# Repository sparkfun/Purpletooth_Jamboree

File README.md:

Purpletooth Jamboree Development Board
==================

Audio support board for the BC127 module from BlueCreation.

[  
*Purpletooth Jamboree Development Board*](https://www.sparkfun.com/products/11924)

Design files and firmware files for the [Purpletooth Jamboree Development Board](https://www.sparkfun.com/products/11924).

Repository Contents
-------------------

* **/Fritzing** - Fritzing components for this board
* **/Hardware** - Eagle PCB layout files
* **/Libraries** - Library files for various platforms
* **/Production** - Files to support SparkFun production

License Information
-------------------

All contents of this repository are released under [Creative Commons Share-alike 4.0](http://creativecommons.org/licenses/by-sa/4.0/).

Authors: Mike Hord @ SparkFun Electonics

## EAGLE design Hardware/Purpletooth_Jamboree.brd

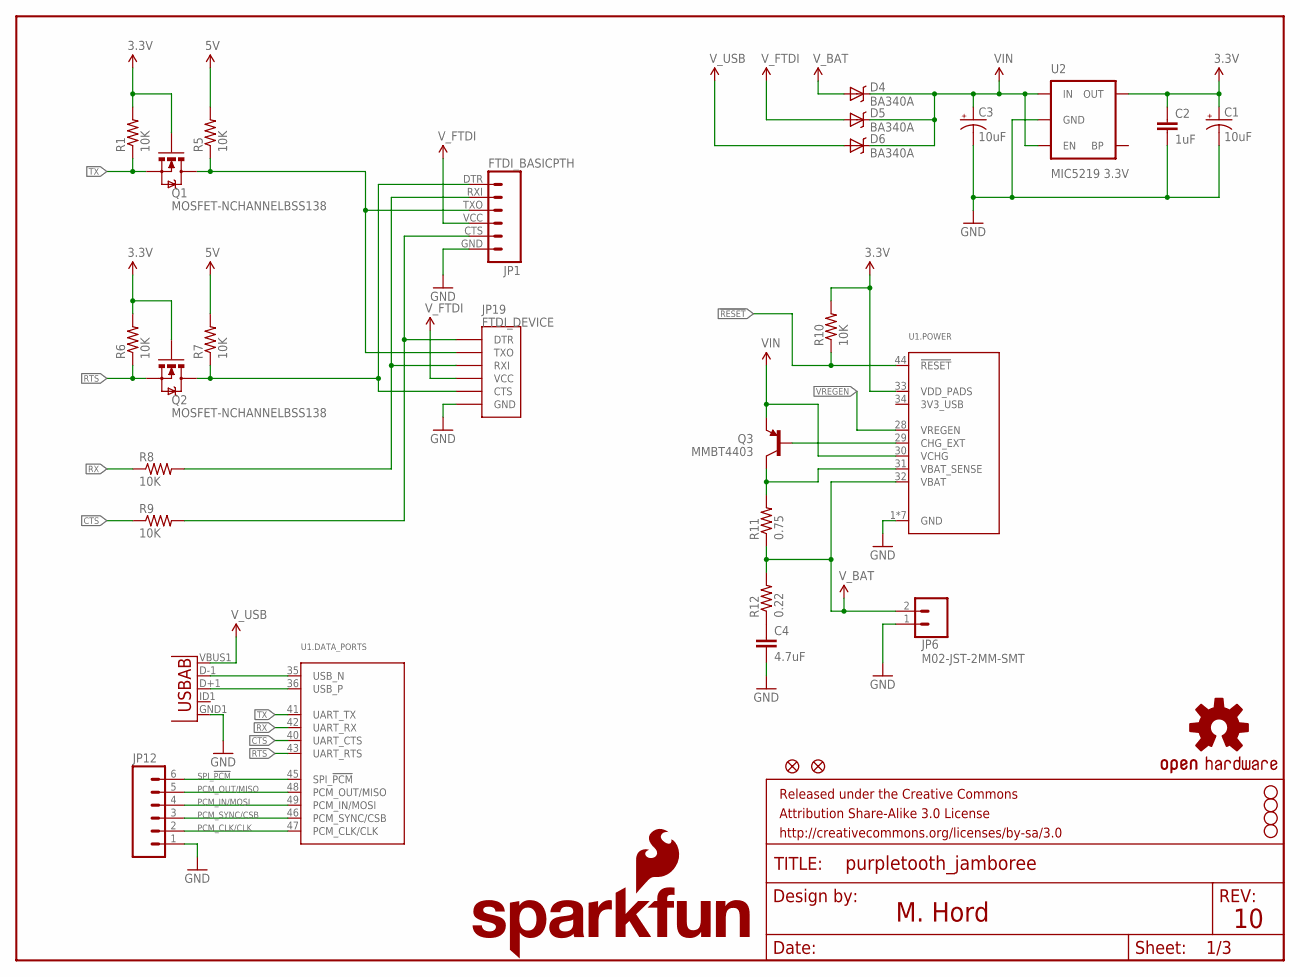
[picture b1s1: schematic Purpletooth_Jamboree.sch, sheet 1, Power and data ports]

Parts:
C1, C3: 10uF; EIA3216
C2: 1uF; 0805
C4: 4.7uF; 0603-CAP
D4, D5, D6: BA340A; SMA-DIODE
FID1, FID2: FIDUCIALUFIDUCIAL; MICRO-FIDUCIAL
FRAME1: FRAME-LETTER; CREATIVE_COMMONS
JP1: FTDI_BASICPTH; FTDI_BASIC
JP2: USB-ABCONN-11794; USB-AB-MICRO-SMD_V03
JP6: M02-JST-2MM-SMT; JST-2-SMD
JP12: M06SIP; 1X06
JP19: FTDI_DEVICE; FTDI_DEVICE_SIDE
LOGO1: OSHW-LOGOM; OSHW-LOGO-M
LOGO2: SFE_LOGO_NAME_FLAME.2_INCH; SFE_LOGO_NAME_FLAME_.2
Q1, Q2: MOSFET-NCHANNELBSS138; SOT23
Q3: MMBT4403; SOT23
R1, R5, R6, R7, R8, R9, R10: 10K; 0603-RES
R11: 0.75; 0805
R12: 0.22; 0805
STANDOFF1, STANDOFF2, STANDOFF3, STANDOFF4: STAND-OFF
U1: BC127EXTRA_PASTE; BC127_XTRA_PASTE
U2: MIC5219 3.3V; SOT23-5

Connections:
3.3V: C1.A (+), C2.1, Q1.1 (G), Q2.1 (G), R1.2, R6.2, R10.2, U1.33 (VDD_PADS), U2.5 (OUT); also elsewhere on the board
5V_CTS: JP1.CTS (5), JP19.P$1 (DTR), R9.2
5V_RTS: JP1.DTR (1), JP19.P$5 (CTS), Q2.3 (D), R7.1
5V_RX: JP1.RXI (2), JP19.P$3 (RXI), R8.2
5V_TX: JP1.TXO (3), JP19.P$2 (TXO), Q1.3 (D), R5.1
!RESET: R10.1, U1.44 (!RESET); also elsewhere on the board
CHG_EXT: Q3.1 (B), U1.29 (CHG_EXT)
CTS: R9.1, U1.40 (UART_CTS)
GND: C1.C (-), C2.2, C3.C (-), C4.2, JP1.GND (6), JP2.GND1 (GND), JP6.1 (2), JP12.1, JP19.P$6 (GND), U1.1 (GND), U1.2 (GND), U1.3 (GND), U1.4 (GND), U1.11 (GND), U1.22 (GND), U1.27 (GND), U2.2 (GND); also elsewhere on the board
unnamed: C4.1, R12.1
PCM_CLK/CLK: JP12.2, U1.47 (PCM_CLK/CLK)
PCM_IN/MOSI: JP12.4, U1.49 (PCM_IN/MOSI)
PCM_OUT/MISO: JP12.5, U1.48 (PCM_OUT/MISO)
PCM_SYNC/CSB: JP12.3, U1.46 (PCM_SYNC/CSB)
RTS: Q2.2 (S), R6.1, U1.43 (UART_RTS)
RX: R8.1, U1.42 (UART_RX)
SPI_!PCM: JP12.6, U1.45 (SPI_!PCM)
TX: Q1.2 (S), R1.1, U1.41 (UART_TX)
USB_N: JP2.D-1 (D-), U1.35 (USB_N)
USB_P: JP2.D+1 (D+), U1.36 (USB_P)
VBAT_SENSE: Q3.3 (C), R11.2, U1.31 (VBAT_SENSE)
VIN: C3.A (+), D4.C, D5.C, D6.C, Q3.2 (E), R5.2, R7.2, U1.30 (VCHG), U2.1 (IN), U2.3 (EN); also elsewhere on the board
VREGEN: U1.28 (VREGEN); also elsewhere on the board
V_BAT: D4.A, JP6.2 (1), R11.1, R12.2, U1.32 (VBAT)
V_FTDI: D5.A, JP1.VCC (4), JP19.P$4 (VCC)
V_USB: D6.A, JP2.VBUS1 (VBUS)

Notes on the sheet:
M. Hord

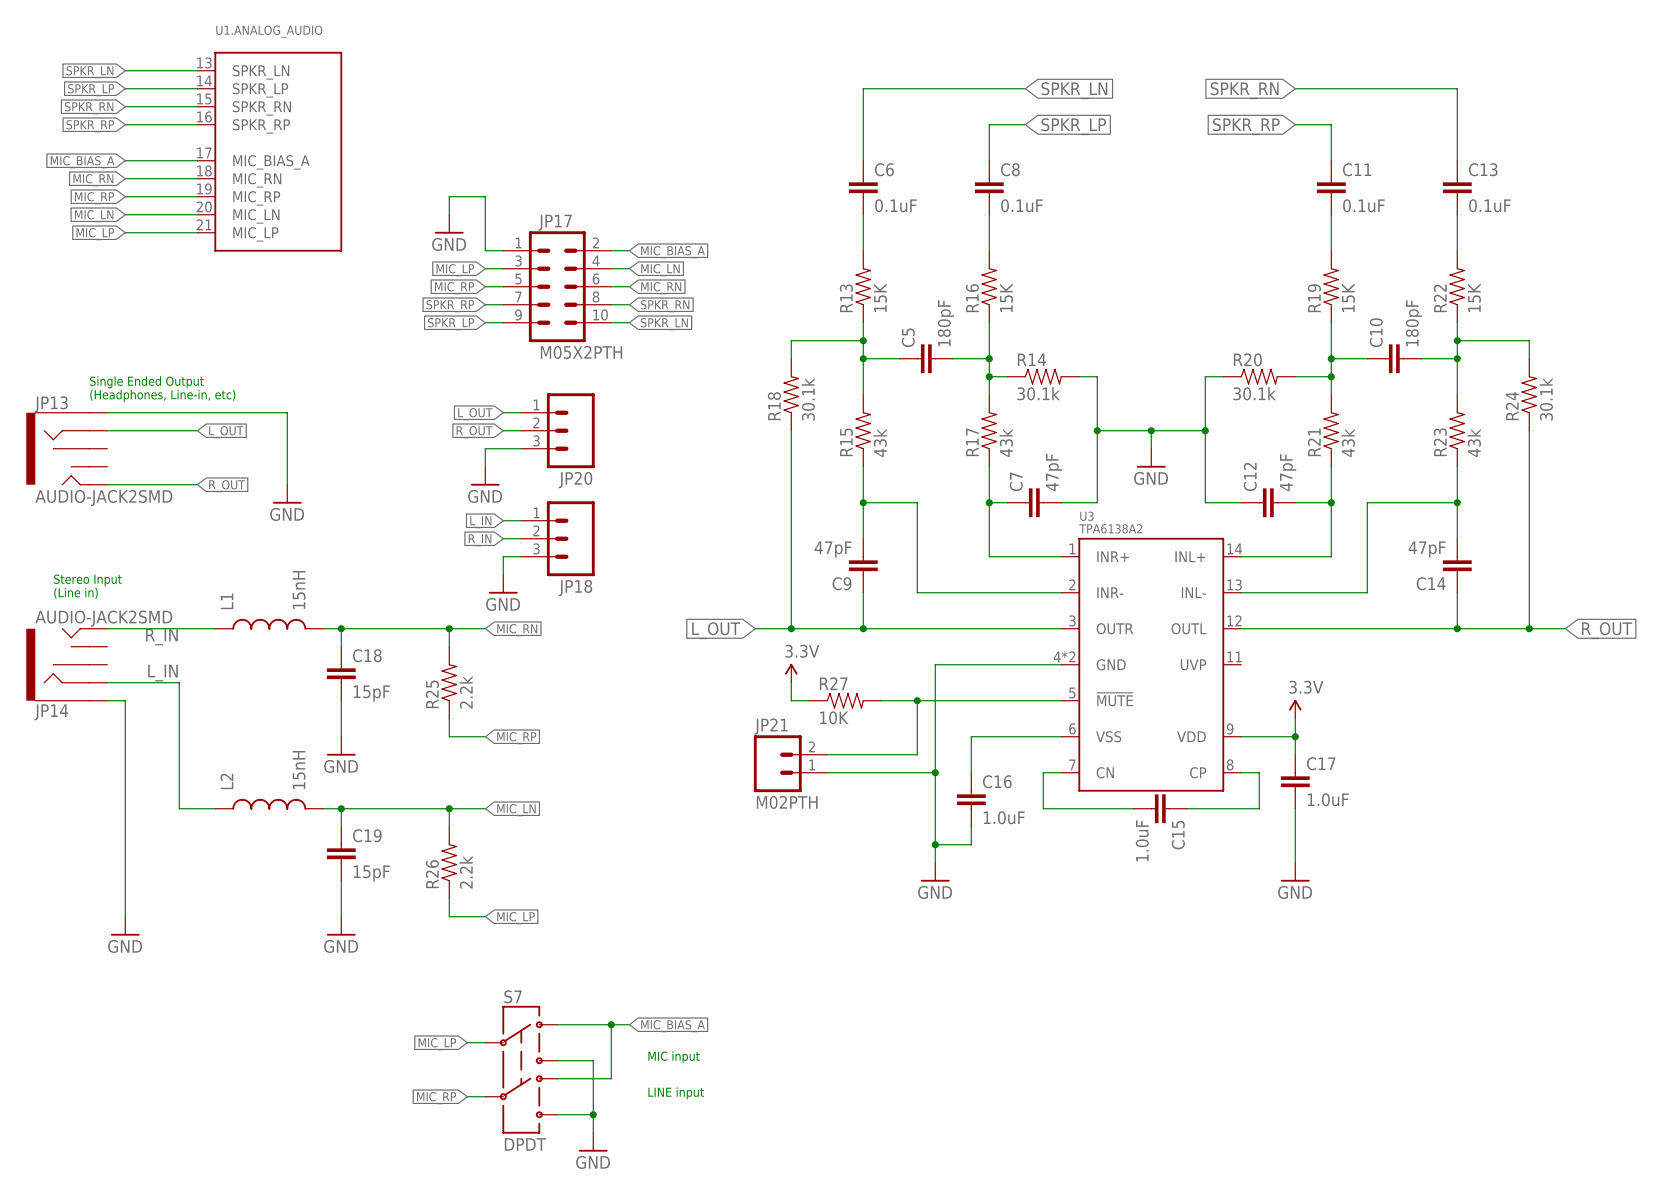
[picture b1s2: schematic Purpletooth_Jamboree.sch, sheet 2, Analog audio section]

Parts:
C5, C10: 180pF; 0603-CAP
C6, C8, C11, C13: 0.1uF; 0603-CAP
C7, C9, C12, C14: 47pF; 0603-CAP
C15, C16, C17: 1.0uF; 0603-CAP
C18, C19: 15pF; 0603-CAP
JP13, JP14: AUDIO-JACK2SMD; AUDIO-JACK-3.5MM-SMD
JP17: M05X2PTH; AVR_ICSP
JP18, JP20: M03PTH; 1X03
JP21: M02PTH; 1X02
L1, L2: 15nH; 0603
R13, R16, R19, R22: 15K; 0603-RES
R14, R18, R20, R24: 30.1k; 0603-RES
R15, R17, R21, R23: 43k; 0603-RES
R25, R26: 2.2k; 0603-RES
R27: 10K; 0603-RES
S7: DPDT; AYZ0202
U1: BC127EXTRA_PASTE; BC127_XTRA_PASTE
U3: TPA6138A2; TSSOP-14

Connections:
3.3V: C17.1, R27.1, U3.9 (VDD); also elsewhere on the board
GND: C7.2, C12.1, C16.2, C17.2, C18.2, C19.2, JP13.SLEEVE, JP14.SLEEVE, JP17.1, JP18.3, JP20.3, JP21.1, R14.2, R20.1, S7.3, S7.6, U3.4 (GND), U3.10 (GND); also elsewhere on the board
L_IN: JP14.RING, JP18.1, L2.1
L_OUT: C9.1, JP13.RING, JP20.1, R18.1, U3.3 (OUTR)
MIC_BIAS_A: JP17.2, S7.1, S7.4, U1.17 (MIC_BIAS_A)
MIC_LN: C19.1, JP17.4, L2.2, R26.2, U1.20 (MIC_LN)
MIC_LP: JP17.3, R26.1, S7.2, U1.21 (MIC_LP)
MIC_RN: C18.1, JP17.6, L1.2, R25.2, U1.18 (MIC_RN)
MIC_RP: JP17.5, R25.1, S7.5, U1.19 (MIC_RP)
unnamed: JP21.2, R27.2, U3.5 (!MUTE)
unnamed: C8.2, R16.2
unnamed: C6.2, R13.2
unnamed: C5.1, R13.1, R15.2, R18.2
unnamed: C9.2, R15.1, U3.2 (INR-)
unnamed: C7.1, R17.1, U3.1 (INR+)
unnamed: C5.2, R14.1, R16.1, R17.2
unnamed: C10.1, R19.1, R20.2, R21.2
unnamed: C12.2, R21.1, U3.14 (INL+)
unnamed: C11.2, R19.2
unnamed: C10.2, R22.1, R23.2, R24.2
unnamed: C13.2, R22.2
unnamed: C14.2, R23.1, U3.13 (INL-)
unnamed: C16.1, U3.6 (VSS)
unnamed: C15.2, U3.7 (CN)
unnamed: C15.1, U3.8 (CP)
R_IN: JP14.TIP, JP18.2, L1.1
R_OUT: C14.1, JP13.TIP, JP20.2, R24.1, U3.12 (OUTL)
SPKR_LN: C6.1, JP17.10, U1.13 (SPKR_LN)
SPKR_LP: C8.1, JP17.9, U1.14 (SPKR_LP)
SPKR_RN: C13.1, JP17.8, U1.15 (SPKR_RN)
SPKR_RP: C11.1, JP17.7, U1.16 (SPKR_RP)

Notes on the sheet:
Single Ended Output (Headphones, Line-in, etc)
Stereo Input (Line in)
MIC input
LINE input

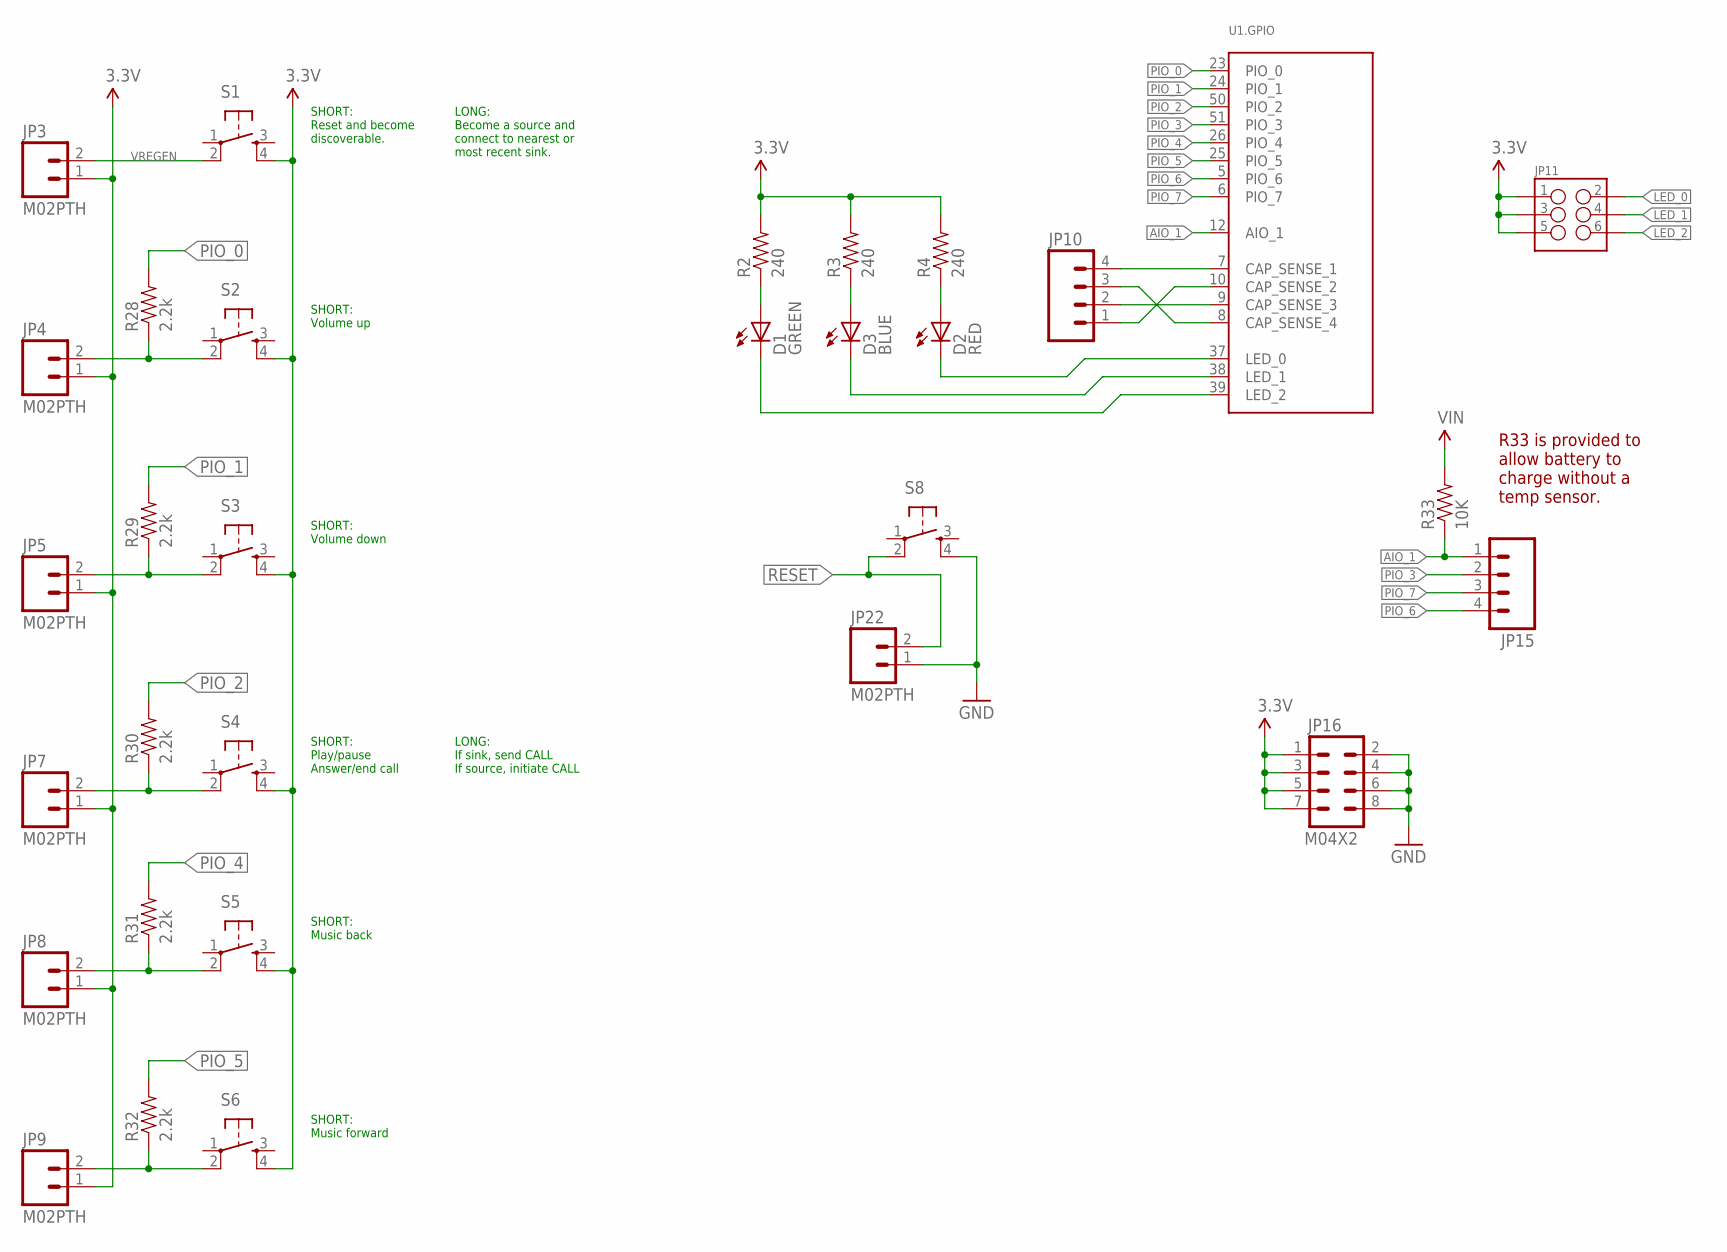
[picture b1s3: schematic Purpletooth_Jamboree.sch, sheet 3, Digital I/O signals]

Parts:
D1: GREEN; LED-0603
D2: RED; LED-0603
D3: BLUE; LED-0603
JP3, JP4, JP5, JP7, JP8, JP9, JP22: M02PTH; 1X02
JP10, JP15: M04PTH; 1X04
JP11: M03X22X3_SILK_SM; 2X3
JP16: M04X2; 2X4
R2, R3, R4: 240; 0603-RES
R28, R29, R30, R31, R32: 2.2k; 0603-RES
R33: 10K; 0603-RES
S1, S2, S3, S4, S5, S6, S8: TAC_SWITCHSMD; TACTILE_SWITCH_SMD
U1: BC127EXTRA_PASTE; BC127_XTRA_PASTE

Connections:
3.3V: JP3.1, JP4.1, JP5.1, JP7.1, JP8.1, JP9.1, JP11.1, JP11.3, JP11.5, JP16.1, JP16.3, JP16.5, JP16.7, R2.2, R3.2, R4.2, S1.4, S2.4, S3.4, S4.4, S5.4, S6.4; also elsewhere on the board
!RESET: JP22.2, S8.2; also elsewhere on the board
AIO_1: JP15.1, R33.1, U1.12 (AIO_1)
CAP_SENSE-4: JP10.3, U1.8 (CAP_SENSE_4)
CAP_SENSE_1: JP10.4, U1.7 (CAP_SENSE_1)
CAP_SENSE_2: JP10.1, U1.10 (CAP_SENSE_2)
CAP_SENSE_3: JP10.2, U1.9 (CAP_SENSE_3)
GND: JP16.2, JP16.4, JP16.6, JP16.8, JP22.1, S8.4; also elsewhere on the board
LED_0: D2.C, JP11.2, U1.37 (LED_0)
LED_1: D3.C, JP11.4, U1.38 (LED_1)
LED_2: D1.C, JP11.6, U1.39 (LED_2)
unnamed: D3.A, R3.1
unnamed: D2.A, R4.1
unnamed: D1.A, R2.1
unnamed: JP4.2, R28.1, S2.2
unnamed: JP5.2, R29.1, S3.2
unnamed: JP7.2, R30.1, S4.2
unnamed: JP8.2, R31.1, S5.2
unnamed: JP9.2, R32.1, S6.2
PIO_0: R28.2, U1.23 (PIO_0)
PIO_1: R29.2, U1.24 (PIO_1)
PIO_2: R30.2, U1.50 (PIO_2)
PIO_3: JP15.2, U1.51 (PIO_3)
PIO_4: R31.2, U1.26 (PIO_4)
PIO_5: R32.2, U1.25 (PIO_5)
PIO_6: JP15.4, U1.5 (PIO_6)
PIO_7: JP15.3, U1.6 (PIO_7)
VIN: R33.2; also elsewhere on the board
VREGEN: JP3.2, S1.2; also elsewhere on the board

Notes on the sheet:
SHORT: Reset and become discoverable.
LONG: Become a source and connect to nearest or most recent sink.
SHORT: Volume up
SHORT: Volume down
SHORT: Play/pause Answer/end call
LONG: If sink, send CALL If source, initiate CALL
SHORT: Music back
SHORT: Music forward
R33 is provided to allow battery to charge without a temp sensor.

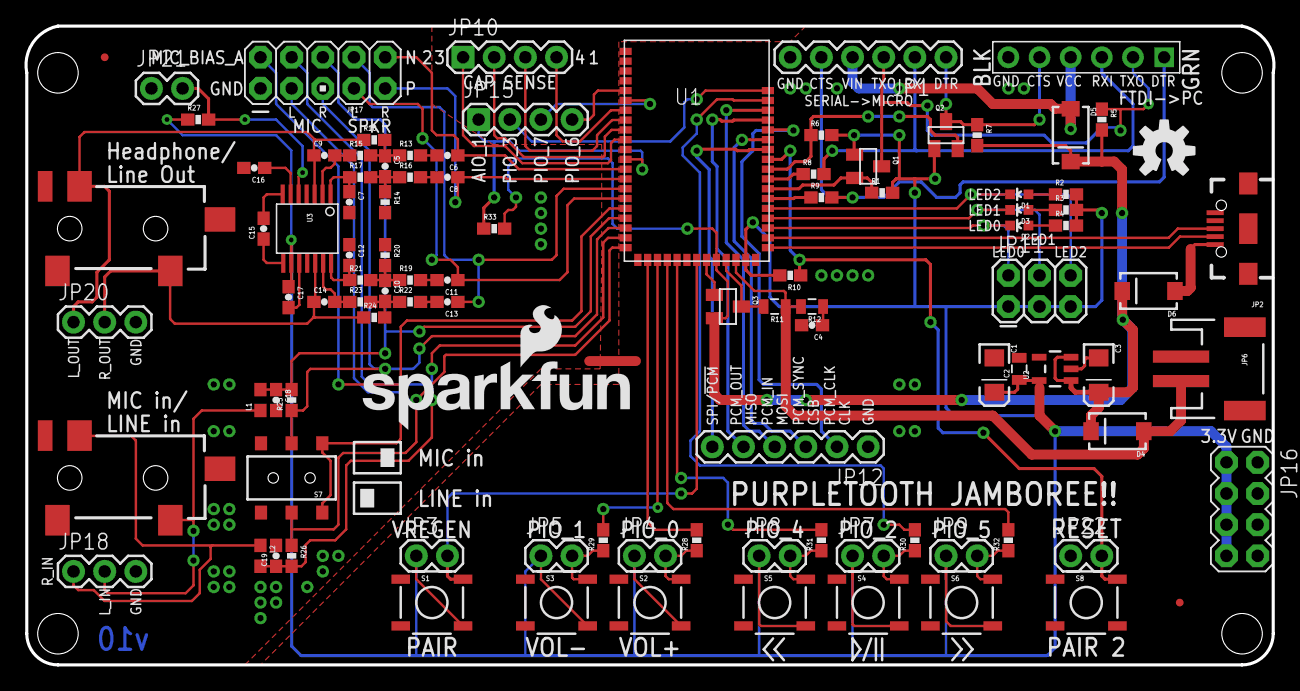
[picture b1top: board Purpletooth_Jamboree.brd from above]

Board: 2 copper layers, 101.7 x 52.1 mm, 105 parts (0 on the bottom side), 79 nets.

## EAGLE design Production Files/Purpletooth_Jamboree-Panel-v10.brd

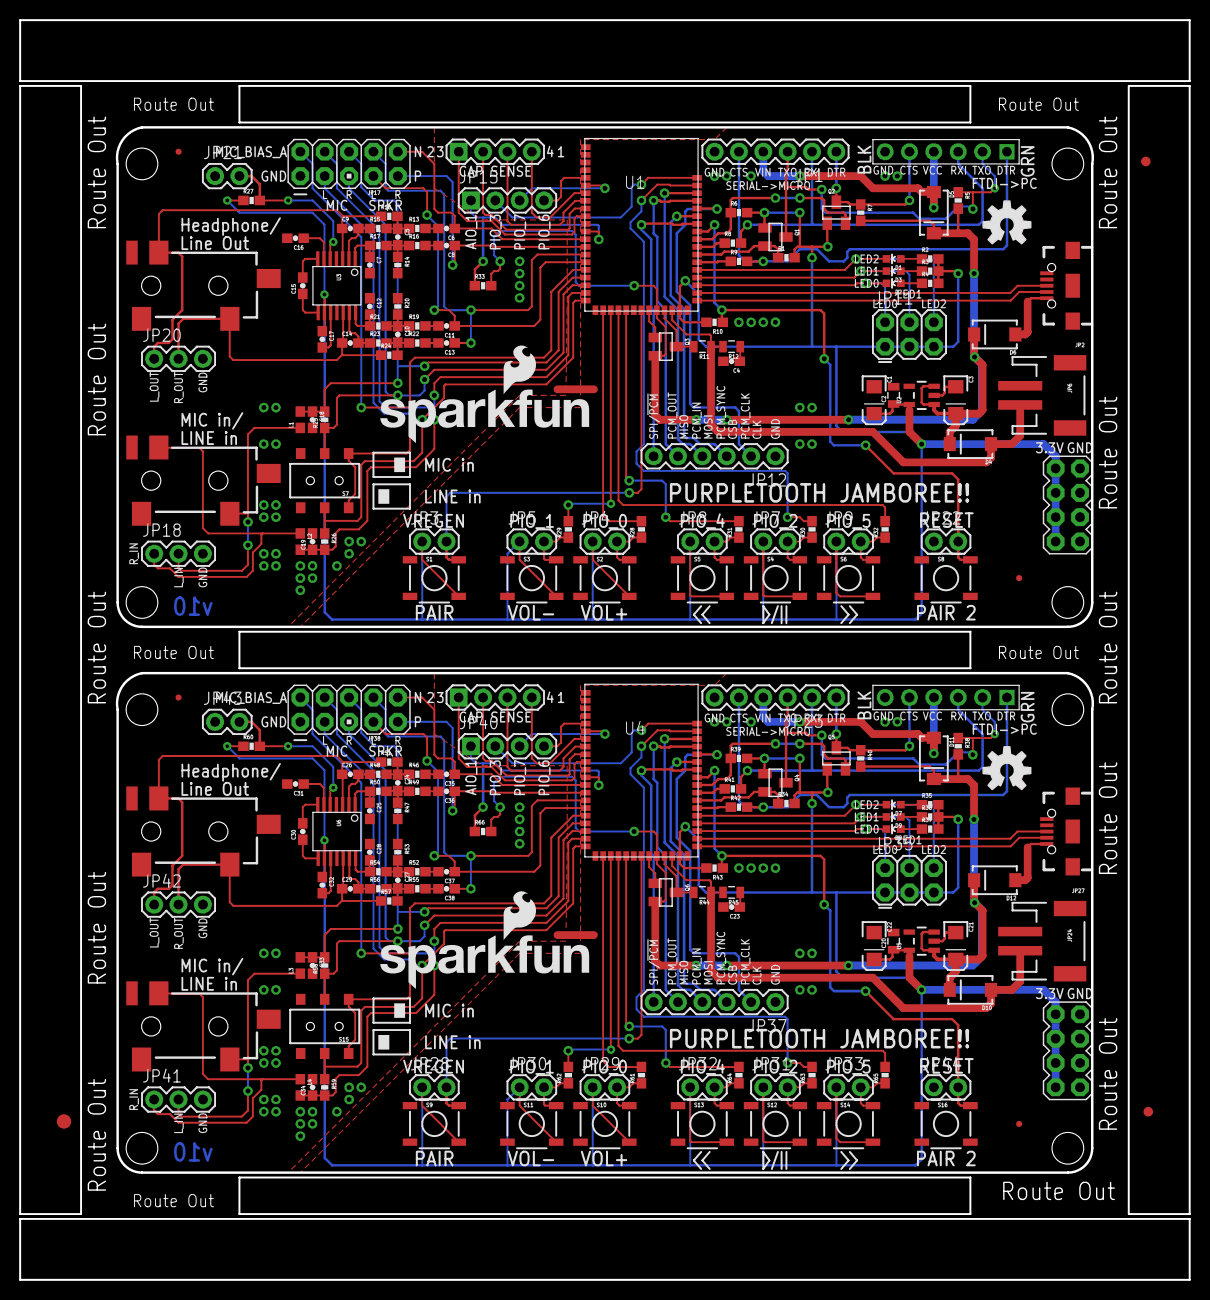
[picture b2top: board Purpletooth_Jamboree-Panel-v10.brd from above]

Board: 2 copper layers, 121.9 x 131.3 mm, 211 parts (0 on the bottom side), 158 nets.

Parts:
C1, C3, C21, C22: 10uF; EIA3216
C2, C20: 1uF; 0805
C4, C23: 4.7uF; 0603-CAP
C5, C10, C24, C27: 180pF; 0603-CAP
C6, C8, C11, C13, C35, C36, C37, C38: 0.1uF; 0603-CAP
C7, C9, C12, C14, C25, C26, C28, C29: 47pF; 0603-CAP
C15, C16, C17, C30, C31, C32: 1.0uF; 0603-CAP
C18, C19, C33, C34: 15pF; 0603-CAP
D1, D7: GREEN; LED-0603
D2, D8: RED; LED-0603
D3, D9: BLUE; LED-0603
D4, D5, D6, D10, D11, D12: BA340A; SMA-DIODE
E$1: FIDUCIAL-1.5X3
E$13, E$14: FIDUCIAL-1X2
FID1, FID2, FID3, FID4: FIDUCIALUFIDUCIAL; MICRO-FIDUCIAL
JP1, JP23: FTDI_BASICPTH; FTDI_BASIC
JP2, JP27: USB-AB-MICRO-SMD_V03
JP3, JP4, JP5, JP7, JP8, JP9, JP21, JP22, JP28, JP29, JP30, JP31, JP32, JP33, JP43, JP44: M02PTH; 1X02
JP6, JP24: M02-JST-2MM-SMT; JST-2-SMD
JP10, JP15, JP34, JP40: 1X04
JP11, JP35: 2X3
JP12, JP37: 1X06
JP13, JP14, JP25, JP26: AUDIO-JACK2SMD; AUDIO-JACK-3.5MM-SMD
JP16, JP36: M04X2; 2X4
JP17, JP38: M05X2PTH; AVR_ICSP
JP18, JP20, JP41, JP42: 1X03
JP19, JP39: FTDI_DEVICE; FTDI_DEVICE_SIDE
L1, L2, L3, L4: 15nH; 0603
LOGO1, LOGO3: OSHW-LOGOM; OSHW-LOGO-M
LOGO2, LOGO4: SFE_LOGO_NAME_FLAME.2_INCH; SFE_LOGO_NAME_FLAME_.2
Q1, Q2, Q4, Q5: MOSFET-NCHANNELBSS138; SOT23
Q3, Q6: MMBT4403; SOT23
R1, R5, R6, R7, R8, R9, R10, R27, R33, R34, R38, R39, R40, R41, R42, R43, R60, R66: 10K; 0603-RES
R2, R3, R4, R35, R36, R37: 240; 0603-RES
R11, R44: 0.75; 0805
R12, R45: 0.22; 0805
R13, R16, R19, R22, R46, R49, R52, R55: 15K; 0603-RES
R14, R18, R20, R24, R47, R51, R53, R57: 30.1k; 0603-RES
R15, R17, R21, R23, R48, R50, R54, R56: 43k; 0603-RES
R25, R26, R28, R29, R30, R31, R32, R58, R59, R61, R62, R63, R64, R65: 2.2k; 0603-RES
S1, S2, S3, S4, S5, S6, S8, S9, S10, S11, S12, S13, S14, S16: TACTILE_SWITCH_SMD
S7, S15: DPDT; AYZ0202
STANDOFF1, STANDOFF2, STANDOFF3, STANDOFF4, STANDOFF5, STANDOFF6, STANDOFF7, STANDOFF8: STAND-OFF
U1, U4: BC127_XTRA_PASTE
U2, U5: MIC5219 3.3V; SOT23-5
U3, U6: TPA6138A2; TSSOP-14

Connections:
3.3V: C1.A, C2.1, C17.1, JP3.1, JP4.1, JP5.1, JP7.1, JP8.1, JP9.1, JP11.1, JP11.3, JP11.5, JP16.1, JP16.3, JP16.5, JP16.7, Q1.1, Q2.1, R1.2, R2.2, R3.2, R4.2, R6.2, R10.2, R27.1, S1.4, S2.4, S3.4, S4.4, S5.4, S6.4, U1.33, U2.5, U3.9
3.3V1: C20.1, C22.A, C32.1, JP28.1, JP29.1, JP30.1, JP31.1, JP32.1, JP33.1, JP35.1, JP35.3, JP35.5, JP36.1, JP36.3, JP36.5, JP36.7, Q4.1, Q5.1, R34.2, R35.2, R36.2, R37.2, R39.2, R43.2, R60.1, S9.4, S10.4, S11.4, S12.4, S13.4, S14.4, U4.33, U5.5, U6.9
5V_CTS: JP1.CTS, JP19.P$1, R9.2
5V_CTS1: JP23.CTS, JP39.P$1, R42.2
5V_RTS: JP1.DTR, JP19.P$5, Q2.3, R7.1
5V_RTS1: JP23.DTR, JP39.P$5, Q5.3, R40.1
5V_RX: JP1.RXI, JP19.P$3, R8.2
5V_RX1: JP23.RXI, JP39.P$3, R41.2
5V_TX: JP1.TXO, JP19.P$2, Q1.3, R5.1
5V_TX1: JP23.TXO, JP39.P$2, Q4.3, R38.1
!RESET: JP22.2, R10.1, S8.2, U1.44
!RESET1: JP44.2, R43.1, S16.2, U4.44
AIO_1: JP15.1, R33.1, U1.12
AIO_2: JP40.1, R66.1, U4.12
CAP_SENSE-1: JP34.3, U4.8
CAP_SENSE-4: JP10.3, U1.8
CAP_SENSE_1: JP10.4, U1.7
CAP_SENSE_2: JP10.1, U1.10
CAP_SENSE_3: JP10.2, U1.9
CAP_SENSE_4: JP34.2, U4.9
CAP_SENSE_5: JP34.4, U4.7
CAP_SENSE_6: JP34.1, U4.10
CHG_EXT: Q3.1, U1.29
CHG_EXT1: Q6.1, U4.29
CTS: R9.1, U1.40
CTS1: R42.1, U4.40
GND: C1.C, C2.2, C3.C, C4.2, C7.2, C12.1, C16.2, C17.2, C18.2, C19.2, JP1.GND, JP2.GND1, JP6.1, JP12.1, JP13.SLEEVE, JP14.SLEEVE, JP16.2, JP16.4, JP16.6, JP16.8, JP17.1, JP18.3, JP19.P$6, JP20.3, JP21.1, JP22.1, R14.2, R20.1, S7.3, S7.6, S8.4, U1.1, U1.2, U1.3, U1.4, U1.11, U1.22, U1.27, U2.2, U3.4, U3.10
GND1: C20.2, C21.C, C22.C, C23.2, C25.2, C28.1, C31.2, C32.2, C33.2, C34.2, JP23.GND, JP24.1, JP25.SLEEVE, JP26.SLEEVE, JP27.GND1, JP36.2, JP36.4, JP36.6, JP36.8, JP37.1, JP38.1, JP39.P$6, JP41.3, JP42.3, JP43.1, JP44.1, R47.2, R53.1, S15.3, S15.6, S16.4, U4.1, U4.2, U4.3, U4.4, U4.11, U4.22, U4.27, U5.2, U6.4, U6.10
LED_0: D2.C, JP11.2, U1.37
LED_1: D3.C, JP11.4, U1.38
LED_2: D1.C, JP11.6, U1.39
LED_3: D7.C, JP35.6, U4.39
LED_4: D9.C, JP35.4, U4.38
LED_5: D8.C, JP35.2, U4.37
L_IN: JP14.RING, JP18.1, L2.1
L_IN1: JP26.RING, JP41.1, L4.1
L_OUT: C9.1, JP13.RING, JP20.1, R18.1, U3.3
L_OUT1: C26.1, JP25.RING, JP42.1, R51.1, U6.3
MIC_BIAS_A: JP17.2, S7.1, S7.4, U1.17
MIC_BIAS_A1: JP38.2, S15.1, S15.4, U4.17
MIC_LN: C19.1, JP17.4, L2.2, R26.2, U1.20
MIC_LN1: C34.1, JP38.4, L4.2, R59.2, U4.20
MIC_LP: JP17.3, R26.1, S7.2, U1.21
MIC_LP1: JP38.3, R59.1, S15.2, U4.21
MIC_RN: C18.1, JP17.6, L1.2, R25.2, U1.18
MIC_RN1: C33.1, JP38.6, L3.2, R58.2, U4.18
MIC_RP: JP17.5, R25.1, S7.5, U1.19
MIC_RP1: JP38.5, R58.1, S15.5, U4.19
unnamed: JP21.2, R27.2, U3.5
unnamed: D3.A, R3.1
unnamed: D9.A, R36.1
unnamed: C8.2, R16.2
unnamed: C6.2, R13.2
unnamed: D2.A, R4.1
unnamed: D1.A, R2.1
unnamed: C5.1, R13.1, R15.2, R18.2
unnamed: C9.2, R15.1, U3.2
unnamed: JP4.2, R28.1, S2.2
unnamed: JP5.2, R29.1, S3.2
unnamed: C7.1, R17.1, U3.1
unnamed: C5.2, R14.1, R16.1, R17.2
unnamed: JP7.2, R30.1, S4.2
unnamed: JP8.2, R31.1, S5.2
unnamed: C10.1, R19.1, R20.2, R21.2
unnamed: C12.2, R21.1, U3.14
unnamed: C11.2, R19.2
unnamed: C10.2, R22.1, R23.2, R24.2
unnamed: C13.2, R22.2
unnamed: C14.2, R23.1, U3.13
unnamed: JP9.2, R32.1, S6.2
unnamed: D8.A, R37.1
unnamed: C16.1, U3.6
unnamed: C15.2, U3.7
unnamed: C15.1, U3.8
unnamed: D7.A, R35.1
unnamed: C4.1, R12.1
unnamed: C23.1, R45.1
unnamed: C36.2, R49.2
unnamed: C35.2, R46.2
unnamed: C24.1, R46.1, R48.2, R51.2
unnamed: C26.2, R48.1, U6.2
unnamed: C25.1, R50.1, U6.1
unnamed: C24.2, R47.1, R49.1, R50.2
unnamed: C27.1, R52.1, R53.2, R54.2
unnamed: C28.2, R54.1, U6.14
unnamed: C37.2, R52.2
unnamed: C27.2, R55.1, R56.2, R57.2
unnamed: C38.2, R55.2
unnamed: C29.2, R56.1, U6.13
unnamed: C31.1, U6.6
unnamed: C30.2, U6.7
unnamed: C30.1, U6.8
unnamed: JP43.2, R60.2, U6.5
unnamed: JP29.2, R61.1, S10.2
unnamed: JP30.2, R62.1, S11.2
unnamed: JP31.2, R63.1, S12.2
unnamed: JP32.2, R64.1, S13.2
unnamed: JP33.2, R65.1, S14.2
PCM_CLK/CLK: JP12.2, U1.47
PCM_CLK/CLK1: JP37.2, U4.47
PCM_IN/MOSI: JP12.4, U1.49
PCM_IN/MOSI1: JP37.4, U4.49
PCM_OUT/MISO: JP12.5, U1.48
PCM_OUT/MISO1: JP37.5, U4.48
PCM_SYNC/CSB: JP12.3, U1.46
PCM_SYNC/CSB1: JP37.3, U4.46
PIO_0: R28.2, U1.23
PIO_1: R29.2, U1.24
PIO_2: R30.2, U1.50
PIO_3: JP15.2, U1.51
PIO_4: R31.2, U1.26
PIO_5: R32.2, U1.25
PIO_6: JP15.4, U1.5
PIO_7: JP15.3, U1.6
PIO_8: R61.2, U4.23
PIO_9: R65.2, U4.25
PIO_10: JP40.4, U4.5
PIO_11: JP40.3, U4.6
PIO_12: R64.2, U4.26
PIO_13: JP40.2, U4.51
PIO_14: R63.2, U4.50
PIO_15: R62.2, U4.24
RTS: Q2.2, R6.1, U1.43
RTS1: Q5.2, R39.1, U4.43
RX: R8.1, U1.42
RX1: R41.1, U4.42
R_IN: JP14.TIP, JP18.2, L1.1
R_IN1: JP26.TIP, JP41.2, L3.1
R_OUT: C14.1, JP13.TIP, JP20.2, R24.1, U3.12
R_OUT1: C29.1, JP25.TIP, JP42.2, R57.1, U6.12
SPI_!PCM: JP12.6, U1.45
SPI_!PCM1: JP37.6, U4.45
SPKR_LN: C6.1, JP17.10, U1.13
SPKR_LN1: C35.1, JP38.10, U4.13
SPKR_LP: C8.1, JP17.9, U1.14
SPKR_LP1: C36.1, JP38.9, U4.14
SPKR_RN: C13.1, JP17.8, U1.15
SPKR_RN1: C38.1, JP38.8, U4.15
SPKR_RP: C11.1, JP17.7, U1.16
SPKR_RP1: C37.1, JP38.7, U4.16
TX: Q1.2, R1.1, U1.41
TX1: Q4.2, R34.1, U4.41
USB_N: JP2.D-1, U1.35
USB_N1: JP27.D-1, U4.35
USB_P: JP2.D+1, U1.36
USB_P1: JP27.D+1, U4.36
VBAT_SENSE: Q3.3, R11.2, U1.31
VBAT_SENSE1: Q6.3, R44.2, U4.31
VIN: C3.A, D4.C, D5.C, D6.C, Q3.2, R5.2, R7.2, R33.2, U1.30, U2.1, U2.3
VIN1: C21.A, D10.C, D11.C, D12.C, Q6.2, R38.2, R40.2, R66.2, U4.30, U5.1, U5.3
VREGEN: JP3.2, S1.2, U1.28
VREGEN1: JP28.2, S9.2, U4.28
V_BAT: D4.A, JP6.2, R11.1, R12.2, U1.32
V_BAT1: D10.A, JP24.2, R44.1, R45.2, U4.32
V_FTDI: D5.A, JP1.VCC, JP19.P$4
V_FTDI1: D11.A, JP23.VCC, JP39.P$4
V_USB: D6.A, JP2.VBUS1
V_USB1: D12.A, JP27.VBUS1

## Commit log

2013-06-13 Initial commit, pre-review
2013-06-18 Roll changes from design review in.
2013-06-18 Files ready for protos
2013-10-07 Roll to next round of protos. - fix FTDI header pinouts - new USB footprint - add resistor to defeat charger temp sense - remove inductor to ground on audio input - fix buttons (add inline resistor, 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
2013-10-07 Library update for connectors lib
2013-10-28 Transition to v10 for production - change labels on board and schematic - move top edge of board .05" up, to prevent module overhang from interfering with panelization
2013-10-28 Added micro fiducial to board
2013-10-28 Created Panel
    normal sized panel
2013-11-20 Add Fritzing Part
2014-01-09 Replaced BC127 PKG w/ BC127_EXTRA_PASTE PKG
    -Replaced the existing BC127 PKG with the BC127_EXTRA_PASTE PKG that
    solved the cold-joint issues on the BC127 Module for the BC127 BOB (adds
    extra paste to module pads).
    -No hardware changes, just a stencil change.
2014-01-09 added over paste for the module to panel
2014-05-15 Changes to README.md
2015-04-27 Squashed 'Libraries/Arduino/' content from commit 6404651
    git-subtree-dir: Libraries/Arduino
    git-subtree-split: 6404651582bfe3aa4f8bdf3988896212e57d584d
2015-04-27 Added library readme
2015-04-27 Modified readme
2017-12-08 Add files via upload
    Added metadata and changed Fritzing part's name to match SFE Fritzing name standards.
2017-12-08 Delete Purpletooth Jamboree!!.fzpz
    removing duplicate

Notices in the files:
parts and their libraries:
SparkFun-RF: Licensing: CC v3.0 Share-Alike You are welcome to use this library for commercial purposes.
SparkFun-Aesthetics: Released under the Creative Commons Attribution Share-Alike 3.0 License
SparkFun-Aesthetics: http://creativecommons.org/licenses/by-sa/3.0
